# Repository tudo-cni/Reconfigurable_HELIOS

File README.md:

## Content of this Repository
This repository contains the code of the operation control center and SBC platform from our paper **Field Performance Evaluation of a
Mechatronic Reflector System in a Private mmWave Network Environment**.

If you use this code, please cite our original work in [Citation](#citation).

## Repository Structure
This paragraph describes the existing folder structure of the repository.
#### Main Folder
- **reconfigurable-helios-platform/**
  - Contains all project files and subfolders.  
##### Subfolders
- **Operation Control Center**
  - Contains all necessary files to run the operation control center
  - **angle mapping**
    - Contains the tables to convert the mechanical azimuth and elevation tilt angles alpha and beta to the corresponding servomotor angles from the top and bottom servomotor
  - **classes**
    - Contains the classes and methods for the operation control center
  - **configurations**
    - Configurations from the operation control center are saved in this folder in txt-files
  - **logos**
    - Contains the svg-files of TU Dortmund University and Communication Networks Institute logos for the operation control center
  - operation_control_center.py
    - Main file of the operation control center
- **Platform Code**
  - Contains the .py files, which run on the SBC

## Quick Start
#### Operation Control Center
This repository contains the code for the Operation Control Center, developed in Python.

To run the Operation Control Center, [NumPy](https://numpy.org/), [PySide6](https://pypi.org/project/PySide6/), to provide access to the QT6.0+ framework, and the [Qt-Material](https://qt-material.readthedocs.io/en/latest/index.html) packages are required.

The code has been tested with the following versions:
- Python: 3.13.0
- Numpy: 2.1.3
- PySide6: 6.9.0
- Qt-Material: 2.14

To start the operation control center, execute **"operation_control_center.py"**.

#### SBC Platform
To run the platform code, you must upload the necessary files from the "Platform Code" folder to the Raspberry Pi Pico, along with the two files "servo.py" and "pca9685.py" from the "[micropython-adafruit-pca9685](https://github.com/adafruit/micropython-adafruit-pca9685)" library.
Please note that these two files are not included in the folder and need to be downloaded from the specified library.

The "main.py" file will then be executed automatically upon starting the single-board computer (SBC).

## Acknowledgement
This work has been supported by the German Federal Ministry of Research, Technology and Space ([BMFTR](https://https://www.bundesregierung.de/breg-en/federal-government/ministries/federal-ministry-of-research-technology-and-space)) in the course of the
[6GEM Research Hub](https://www.6gem.de/en/) under the grant number 16KISK038.

## Citation
If you use this code in any of your publications, please cite our work (author's version) as:
```
@article{Haeger/etal/2025b,
	Author = {S. H{\"a}ger, M. Kaudewitz, F. Schmickmann, S. B{\"o}cker, and C. Wietfeld},
	Title = {Field Performance Evaluation of a Mechatronic Reflector System in a Private {mmWave} Network Environment},
	Journal = {IEEE Open Journal of the Communications Society},
	Month= jun, 
	Year = {2025},
	Vol = {6},
	Pages = {5005-5029},
	Doi = {10.1109/OJCOMS.2025.3572723},
	Project = {6GEM}, 
}
```

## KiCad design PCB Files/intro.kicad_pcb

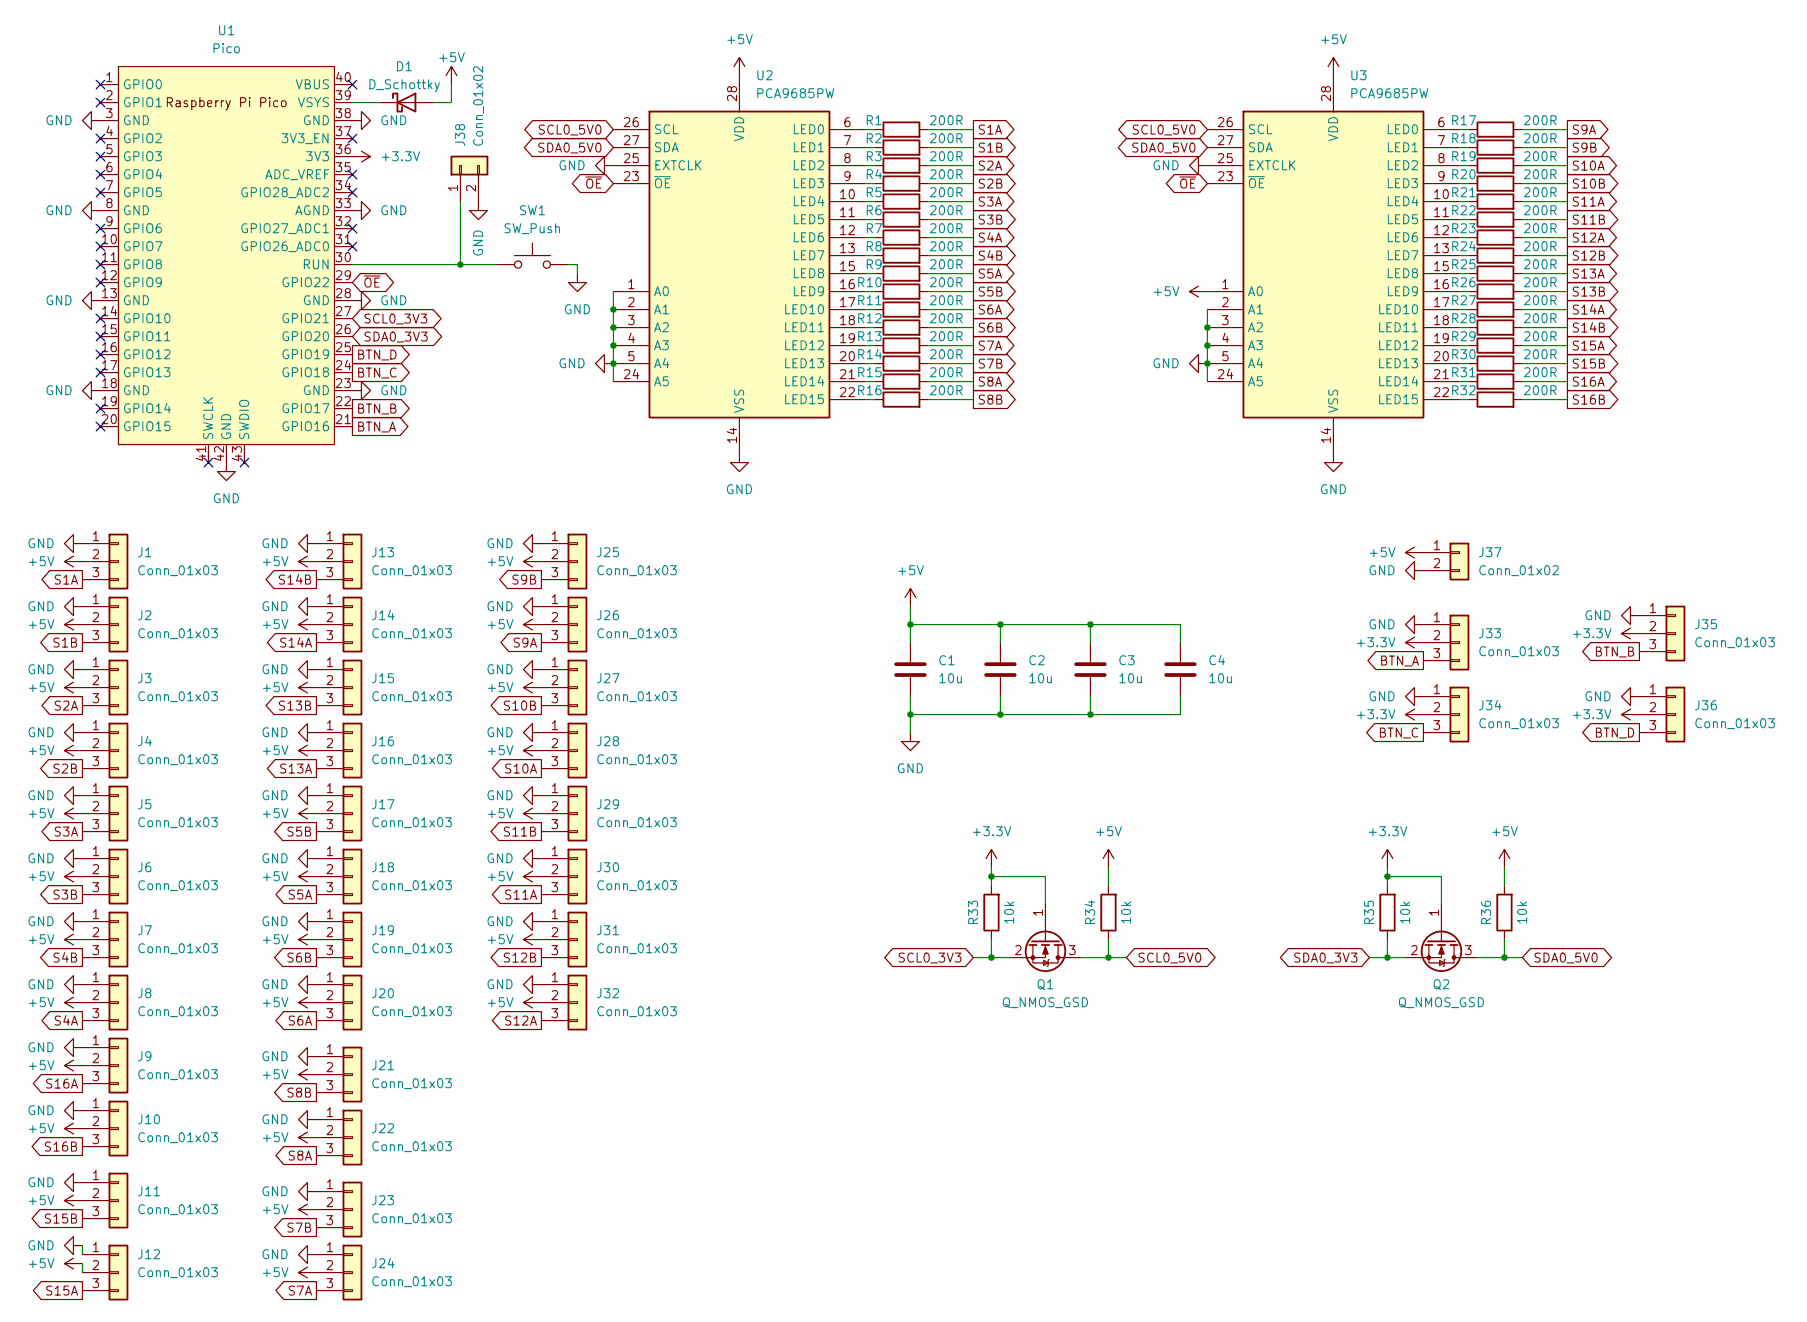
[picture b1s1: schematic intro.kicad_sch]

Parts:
C1, C2, C3, C4: 10u; C_0603_1608Metric
D1: D_Schottky; D_SOD-323_HandSoldering
J1, J2, J3, J4, J5, J6, J7, J8, J9, J10, J11, J12, J13, J14, J15, J16, J17, J18, J19, J20, J21, J22, J23, J24, J25, J26, J27, J28, J29, J30, J31, J32, J33, J34, J35, J36: Conn_01x03; PinHeader_1x03_P2.54mm_Vertical
J37: Conn_01x02; AMASS_XT60PW-M_1x02_P7.20mm_Horizontal
J38: Conn_01x02; PinHeader_1x02_P2.54mm_Vertical
Q1, Q2: Q_NMOS_GSD; SOT-23-3
R1, R2, R3, R4, R5, R6, R7, R8, R9, R10, R11, R12, R13, R14, R15, R16, R17, R18, R19, R20, R21, R22, R23, R24, R25, R26, R27, R28, R29, R30, R31, R32: 200R; R_0603_1608Metric
R33, R34, R35, R36: 10k; R_0603_1608Metric
SW1: SW_Push; SW_SPST_TL3342
U1: Pico; RPi_Pico_W_SMD_TH
U2, U3: PCA9685PW; TSSOP-28_4.4x9.7mm_P0.65mm

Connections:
+3.3V: J33.2, J34.2, J35.2, J36.2, Q1.1 (G), Q2.1 (G), R33.2, R35.2, U1.36 (3V3)
+5V: C1.1, C2.1, C3.1, C4.1, D1.2 (A), J1.2, J2.2, J3.2, J4.2, J5.2, J6.2, J7.2, J8.2, J9.2, J10.2, J11.2, J12.2, J13.2, J14.2, J15.2, J16.2, J17.2, J18.2, J19.2, J20.2, J21.2, J22.2, J23.2, J24.2, J25.2, J26.2, J27.2, J28.2, J29.2, J30.2, J31.2, J32.2, J37.1, R34.2, R36.2, U2.28 (VDD), U3.1 (A0), U3.28 (VDD)
BTN_A: J33.3, U1.21 (GPIO16)
BTN_B: J35.3, U1.22 (GPIO17)
BTN_C: J34.3, U1.24 (GPIO18)
BTN_D: J36.3, U1.25 (GPIO19)
GND: C1.2, C2.2, C3.2, C4.2, J1.1, J2.1, J3.1, J4.1, J5.1, J6.1, J7.1, J8.1, J9.1, J10.1, J11.1, J12.1, J13.1, J14.1, J15.1, J16.1, J17.1, J18.1, J19.1, J20.1, J21.1, J22.1, J23.1, J24.1, J25.1, J26.1, J27.1, J28.1, J29.1, J30.1, J31.1, J32.1, J33.1, J34.1, J35.1, J36.1, J37.2, J38.2, SW1.2, U1.3 (GND), U1.8 (GND), U1.13 (GND), U1.18 (GND), U1.23 (GND), U1.28 (GND), U1.33 (AGND), U1.38 (GND), U1.42 (GND), U2.1 (A0), U2.2 (A1), U2.3 (A2), U2.4 (A3), U2.5 (A4), U2.14 (VSS), U2.24 (A5), U2.25 (EXTCLK), U3.2 (A1), U3.3 (A2), U3.4 (A3), U3.5 (A4), U3.14 (VSS), U3.24 (A5), U3.25 (EXTCLK)
unnamed: D1.1 (K), U1.39 (VSYS)
unnamed: J38.1, SW1.1, U1.30 (RUN)
unnamed: R1.1, U2.6 (LED0)
unnamed: R2.1, U2.7 (LED1)
unnamed: R3.1, U2.8 (LED2)
unnamed: R4.1, U2.9 (LED3)
unnamed: R5.1, U2.10 (LED4)
unnamed: R6.1, U2.11 (LED5)
unnamed: R7.1, U2.12 (LED6)
unnamed: R8.1, U2.13 (LED7)
unnamed: R9.1, U2.15 (LED8)
unnamed: R10.1, U2.16 (LED9)
unnamed: R11.1, U2.17 (LED10)
unnamed: R12.1, U2.18 (LED11)
unnamed: R13.1, U2.19 (LED12)
unnamed: R14.1, U2.20 (LED13)
unnamed: R15.1, U2.21 (LED14)
unnamed: R16.1, U2.22 (LED15)
unnamed: R17.1, U3.6 (LED0)
unnamed: R18.1, U3.7 (LED1)
unnamed: R19.1, U3.8 (LED2)
unnamed: R20.1, U3.9 (LED3)
unnamed: R21.1, U3.10 (LED4)
unnamed: R22.1, U3.11 (LED5)
unnamed: R23.1, U3.12 (LED6)
unnamed: R24.1, U3.13 (LED7)
unnamed: R25.1, U3.15 (LED8)
unnamed: R26.1, U3.16 (LED9)
unnamed: R27.1, U3.17 (LED10)
unnamed: R28.1, U3.18 (LED11)
unnamed: R29.1, U3.19 (LED12)
unnamed: R30.1, U3.20 (LED13)
unnamed: R31.1, U3.21 (LED14)
unnamed: R32.1, U3.22 (LED15)
S1A: J1.3, R1.2
S1B: J2.3, R2.2
S2A: J3.3, R3.2
S2B: J4.3, R4.2
S3A: J5.3, R5.2
S3B: J6.3, R6.2
S4A: J8.3, R7.2
S4B: J7.3, R8.2
S5A: J18.3, R9.2
S5B: J17.3, R10.2
S6A: J20.3, R11.2
S6B: J19.3, R12.2
S7A: J24.3, R13.2
S7B: J23.3, R14.2
S8A: J22.3, R15.2
S8B: J21.3, R16.2
S9A: J26.3, R17.2
S9B: J25.3, R18.2
S10A: J28.3, R19.2
S10B: J27.3, R20.2
S11A: J30.3, R21.2
S11B: J29.3, R22.2
S12A: J32.3, R23.2
S12B: J31.3, R24.2
S13A: J16.3, R25.2
S13B: J15.3, R26.2
S14A: J14.3, R27.2
S14B: J13.3, R28.2
S15A: J12.3, R29.2
S15B: J11.3, R30.2
S16A: J9.3, R31.2
S16B: J10.3, R32.2
SCL0_3V3: Q1.2 (S), R33.1, U1.27 (GPIO21)
SCL0_5V0: Q1.3 (D), R34.1, U2.26 (SCL), U3.26 (SCL)
SDA0_3V3: Q2.2 (S), R35.1, U1.26 (GPIO20)
SDA0_5V0: Q2.3 (D), R36.1, U2.27 (SDA), U3.27 (SDA)
~OE: U1.29 (GPIO22), U2.23 (~OE), U3.23 (~OE)

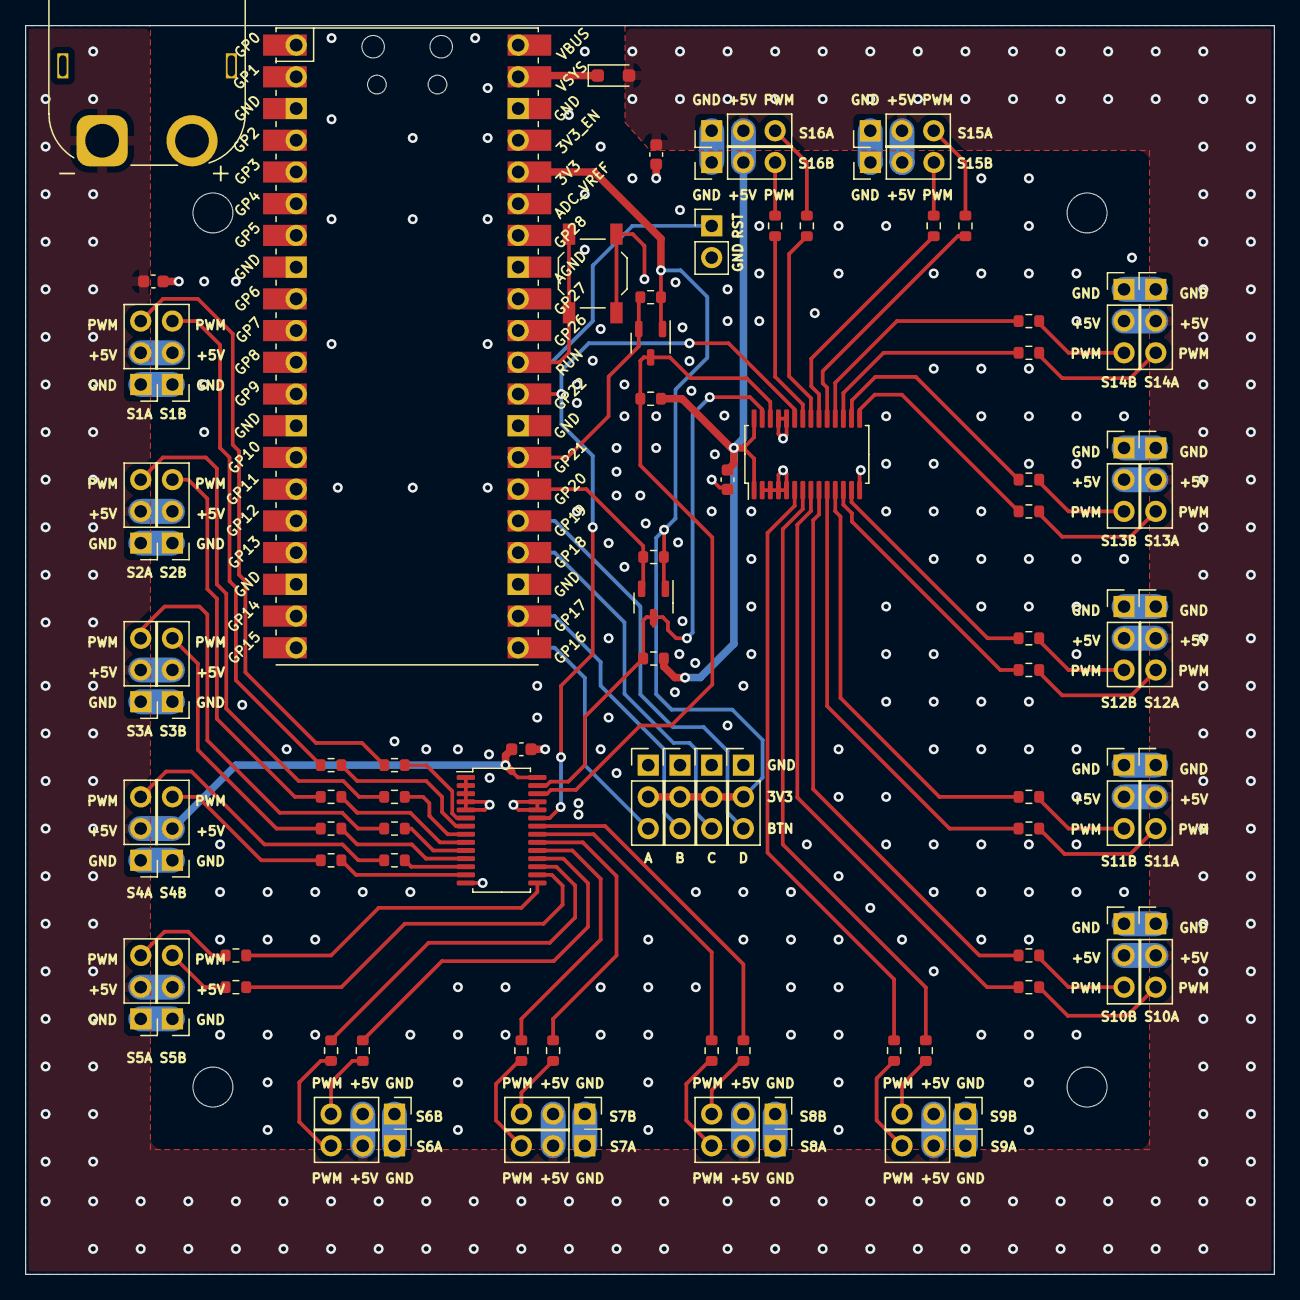
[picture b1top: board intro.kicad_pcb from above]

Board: 4 copper layers, 100.0 x 100.0 mm, 85 parts (0 on the bottom side), 78 nets.
